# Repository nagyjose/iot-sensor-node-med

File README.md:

# IoT Sensor Node Medium (`iot-sensor-node-med`)

> Compact, battery-powered wireless IoT environmental monitoring node based on the Raspberry Pi Pico W, featuring Li-Ion charging, hardware battery protection, zero-quiescent voltage monitoring, and multiple sensor/display interfaces.

**Project Status:** Completed & Functional | **Technologies:** Autodesk Eagle, Hardware PCB Design, RP2040 / Pico W, MicroPython / C++

---

## 1. Overview & Key Features

The **IoT Sensor Node Medium** is a dedicated hardware board tailored for low-power remote environmental sensing, smart home telemetry, and weather monitoring. Designed around the **Raspberry Pi Pico W** (RP2040 + CYW43439 Wi-Fi & Bluetooth LE), the board integrates all necessary power management, battery safety circuitry, and sensor interfaces on a compact 49 × 74 mm two-layer PCB.

### Key Highlights
- **Microcontroller:** Raspberry Pi Pico W socket (RP2040 dual-core ARM Cortex-M0+ up to 133 MHz, 264 KB SRAM, 2 MB QSPI Flash, onboard 2.4 GHz 802.11n Wi-Fi and BLE 5.2).
- **Power Architecture:**
  - Standard 18650 Li-Ion / Li-Po single-cell battery holder footprint.
  - **Microchip MCP73831T** linear Li-Ion charge management IC with charging indicator LED (`D1`).
  - **Diodes Inc. AP9101C** dedicated battery protection controller paired with **BXT280N02B** dual N-MOSFET (overcharge, overdischarge cutoff, and short-circuit protection).
  - **Automatic Power Path:** Ultra-low drop P-channel MOSFET (`YJL2301D`) power switch and Schottky diode (`STPS1L30`) automatically transition between USB 5 V (VBUS) and battery power.
- **Ultra-Low Power Battery Monitoring:**
  - **LM4040** precision shunt voltage reference on the RP2040 `ADC_REF` pin for rock-solid ADC measurements regardless of supply variations.
  - Switched resistor divider (8.2 kΩ / 22 kΩ) controlled via GP3 (`EN-MEAS-1`) using dual MOSFETs (`T4` / `T6`). Zero current is consumed by the voltage divider during deep sleep!
  - Analog input clamped with dual Schottky diodes (`RB751V40T1G`) to protect the RP2040 ADC input (`GP27`).
- **Telemetry & Sensor Interfaces:**
  - **AM2302 (DHT22):** Relative humidity and ambient temperature digital sensor on `GP14`.
  - **DS18B20:** 1-Wire high-accuracy digital temperature sensor on `GP15`.
  - **OLED Display Header:** 4-pin header for 0.96" or 1.3" I2C OLED displays (SSD1306 / SH1106) on `I2C0` (`GP4` / `GP5`).
  - **nRF24L01+ 2.4 GHz RF Header:** SPI socket for Nordic nRF24L01+ wireless transceiver module on `SPI0` (`GP16`–`GP20`) for long-range ultra-low-power radio mesh networks.
  - **General Purpose Breakout:** Available headers for `UART0` (TX/RX), additional ADC channels (`GP26`, `GP28`), and multiple digital GPIOs.

---

## 2. Architecture & Block Diagram

```mermaid
flowchart TD
    subgraph PowerSystem["⚡ Power Management & Protection"]
        USB["USB 5V (VBUS)"] --> CHG["MCP73831T<br/>Li-Ion Charger"]
        USB --> PATH["Power Path Switch<br/>(P-MOS T3 & D3)"]
        BAT["18650 Li-Ion Cell"] --> PROT["AP9101C + Dual NMOS<br/>Battery Protection"]
        CHG --> PROT
        PROT --> PATH
        PATH --> VSYS["VSYS (System Rail)"]
        VSYS --> PICO_REG["Pico W Onboard RT6154<br/>Buck-Boost Converter"]
        PICO_REG --> 3V3["3.3V Power Rail"]
    end

    subgraph Monitoring["🔋 Precision Battery Measurement"]
        PROT -->|VBATT| DIV["Switched Divider<br/>(8.2k / 22k)"]
        MCU -->|GP3: EN-MEAS-1| GATE["MOSFET Switch<br/>(T4 / T6)"]
        GATE --> DIV
        DIV -->|VADC-1| MCU_ADC["ADC1 (GP27)<br/>Clamped & Filtered"]
        VREF["LM4040 Precision Ref"] -->|ADC_REF| MCU_ADC
    end

    subgraph MCU["🧠 Processing & Core Connectivity"]
        PICO["Raspberry Pi Pico W<br/>(RP2040 MCU)"]
        WIFI["Onboard CYW43439<br/>Wi-Fi 802.11n & BLE 5.2"]
    end

    subgraph Peripherals["📡 Sensors & Communication"]
        DHT["AM2302 / DHT22<br/>(Humidity & Temp)"] ---|GP14| MCU
        DS["DS18B20<br/>(1-Wire Temp)"] ---|GP15| MCU
        OLED["OLED Display<br/>(SSD1306 / SH1106)"] ---|I2C0: GP4/GP5| MCU
        NRF["nRF24L01+ Module<br/>(2.4 GHz RF)"] ---|SPI0: GP16-GP20| MCU
        UART["UART0 Header<br/>(Serial Debug / GPS)"] ---|GP0 / GP1| MCU
    end

    3V3 --> MCU
    3V3 --> Peripherals
```

---

## 3. Schematic & Circuit Diagram

📄 [Open original high-resolution schematic (PDF)](Sensor-node_med.pdf)

---

## 4. Hardware Specifications & Pin Mapping

### Microcontroller Pin Allocation

| Pico W Pin | Eagle Net Name | Hardware Function / Connected Device | Notes |
| :--- | :--- | :--- | :--- |
| **GP0** | `UART0-TX` | Serial UART TX | Breakout header / Debug |
| **GP1** | `UART0-RX` | Serial UART RX | Breakout header / Debug |
| **GP2** | `EN-MEAS-0` | Auxiliary measurement enable | Reserved / expansion |
| **GP3** | `EN-MEAS-1` | Battery measurement enable | Gates T4 & T6 MOSFETs |
| **GP4** | `I2C0-SDA` | I2C Data bus | Connected to OLED header (pin 4) |
| **GP5** | `I2C0-SCK` | I2C Clock bus | Connected to OLED header (pin 3) |
| **GP6–GP13** | `GPIO-2`..`GPIO-9`| General-purpose digital I/O | Header breakout pins |
| **GP14** | `AM2302-DATA` | AM2302 / DHT22 Data line | Pulled up to 3.3V with 4.7 kΩ (R15) |
| **GP15** | `1-WIRE-DQ` | DS18B20 1-Wire Data line | Pulled up to 3.3V with 4.7 kΩ (R16) |
| **GP16** | `SPI0-MISO` | nRF24L01+ MISO | SPI0 Data in |
| **GP17** | `SPI0-CSN` | nRF24L01+ Chip Select Not | SPI0 CSN |
| **GP18** | `SPI0-SCK` | nRF24L01+ Clock | SPI0 SCK |
| **GP19** | `SPI0-MOSI` | nRF24L01+ MOSI | SPI0 Data out |
| **GP20** | `RADIO-EN` | nRF24L01+ Chip Enable (CE) | Radio TX/RX enable |
| **GP26** | `VADC-0` | ADC Channel 0 | External analog input |
| **GP27** | `VADC-1` | ADC Channel 1 | Switched battery voltage divider input |
| **GP28** | `VADC-2` | ADC Channel 2 | External analog input |
| **ADC_REF** | `ADC-REF` | RP2040 ADC Reference voltage | Tied to LM4040 precision shunt reference |

### Power & Battery Circuit Components

| Component | Part / Package | Value / Function | Description |
| :--- | :--- | :--- | :--- |
| **U1** | MCP73831T-2ACI/OT (SOT-23-5) | Li-Ion Linear Charger | $I_{CHG} = 1000V / R_{PROG} = 1000 / 2\,\text{k}\Omega \approx 500\,\text{mA}$ |
| **U2** | AP9101CA6-ANTRG1 (SOT-26) | Battery Protection IC | Overvoltage, undervoltage cutoff, overcurrent |
| **T1** | BXT280N02B (TSSOP-8) | Dual N-MOSFET (20V, 6A) | Low-side power cutoff switch for AP9101 |
| **T3** | YJL2301D (SOT-23) | P-MOSFET (-20V, -2.8A) | Low-loss automatic power path switch |
| **D3** | STPS1L30 (SMA) | Schottky Diode (30V, 1A) | VBUS reverse protection / power supply |
| **D13** | LM4040AIM3-2.5 or 3.0 (SOT-23) | Shunt Reference | Precision reference voltage for ADC |
| **T4 / T6** | BXT280N02B / YJL2301D | NMOS + PMOS Switch | Gates $V_{BATT}$ divider to prevent sleep discharge |

---

## 5. PCB Design & Physical Dimensions

- **PCB Dimensions:** 48.95 mm × 73.90 mm (1.93" × 2.91")
- **Layer Count:** 2 layers (Top Copper, Bottom Copper)
- **Mounting:** Rounded corners, designed to fit inside standard plastic enclosure or snap-fit 3D-printed housing.
- **Top Side:** Houses the Raspberry Pi Pico W module, OLED display header, nRF24L01+ socket, sensors, and status LEDs.
- **Bottom Side:** Accommodates the single 18650 spring battery clip (`CON_18650`), protection IC, and power path semiconductors.

---

## 6. Repository Structure

```text
.
├── docs/
│   └── images/
│       └── schematic.png  # High-resolution schematic preview (180 DPI)
├── Sensor-node_med.sch    # Autodesk Eagle schematic
├── Sensor-node_med.brd    # Autodesk Eagle PCB layout
├── Sensor-node_med.pdf    # Complete schematic and board PDF documentation
├── Sensor-node_med.dru    # Design rules specification (DRC)
├── Sensor-node_med.scr    # Eagle layer & color setup script
├── .gitignore             # Eagle & OS backup filter
└── README.md              # Project documentation
```

---

## 7. How to Use & Firmware Deployment

### Hardware Assembly & Inspection
1. Inspect PCB solder joints around the SOT-23 and SOT-26 packages (`MCP73831T`, `AP9101C`, MOSFETs).
2. Insert a standard protected or unprotected 18650 cell into the battery clips observing correct polarity.
3. Plug in USB: `D1` will illuminate while charging and extinguish when charging completes.

### Firmware Support
This board is fully compatible with MicroPython, CircuitPython, and C/C++ (Pico SDK / Arduino IDE).
To read the battery voltage with zero idle power draw in MicroPython:

```python
from machine import Pin, ADC
import time

# Enable battery measurement divider
en_meas = Pin(3, Pin.OUT)
adc_bat = ADC(Pin(27))

def read_battery_voltage():
    en_meas.value(1)       # Power on the resistor divider
    time.sleep_us(50)      # Wait for rail stabilization
    raw = adc_bat.read_u16()
    en_meas.value(0)       # Immediately shut down divider to save battery

    # Conversion formula based on 8.2k / 22k divider ratio and reference voltage
    v_measured = (raw / 65535.0) * 3.3
    v_batt = v_measured * (8.2 + 22.0) / 22.0
    return v_batt
```

---

## 8. Relations & Ecosystem Links

This project is part of a modular IoT sensor ecosystem:
- **[`iot-sensor-node-max`](https://github.com/nagyjose/iot-sensor-node-max):** Sister project providing a dual-18650 battery bank, dual independent chargers, dual I2C expansion headers, dual SPI expansion headers, and external ADC input.
- **[`pico-w-iot-nodes`](https://github.com/nagyjose/pico-w-iot-nodes):** MicroPython firmware repository implementing BLE GATT telemetry, MQTT over Wi-Fi, DS18B20 / AM2302 acquisition, and deep sleep cycles.
- **[`ble-sensor-gui`](https://github.com/nagyjose/ble-sensor-gui):** PyQt5 / QML desktop application for real-time visualization of telemetry and sensor feeds.

---

## 9. License & Author

- **Author:** Josef Nagy (`nagyjose`)
- **Design Tool:** Autodesk Eagle v9.x
- **License:** Open Hardware / MIT License

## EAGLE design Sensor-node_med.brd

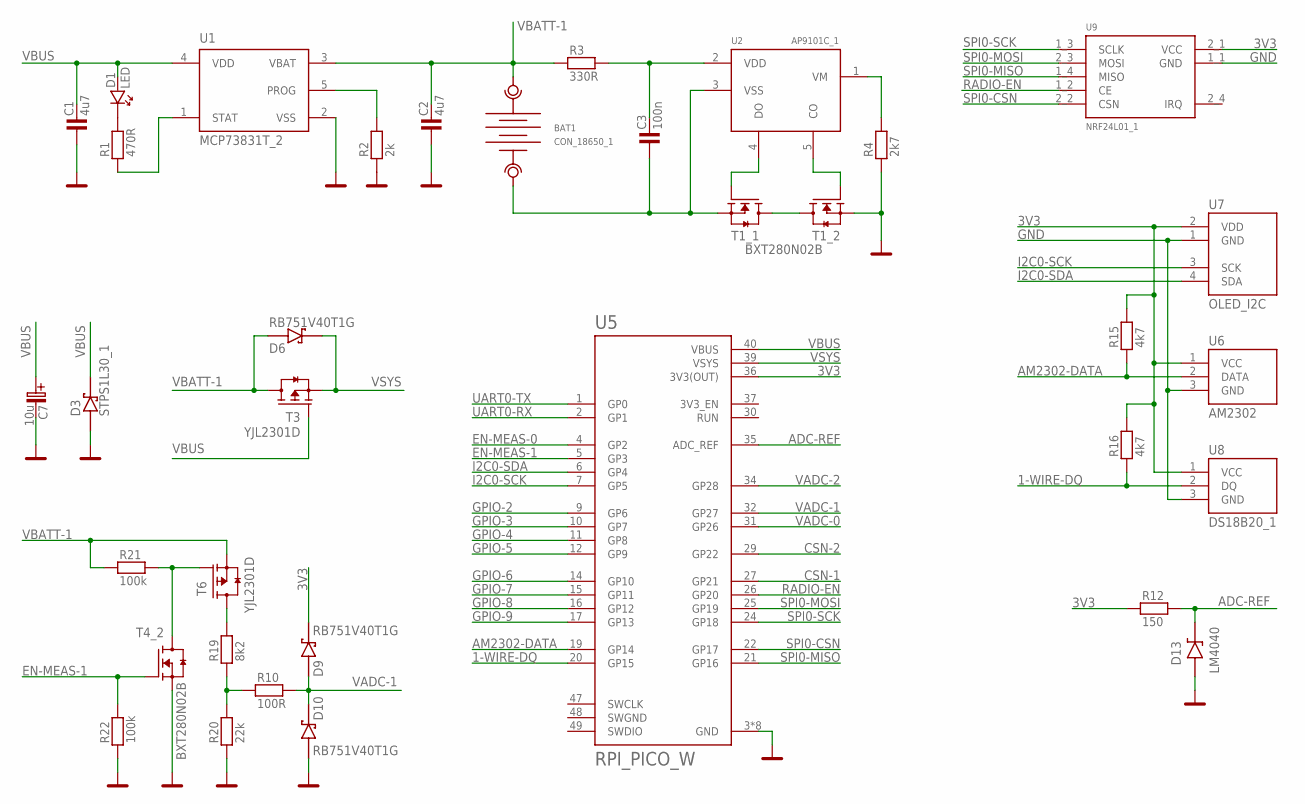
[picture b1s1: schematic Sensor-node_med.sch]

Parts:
BAT1: CON_18650_1; BATTERY_PADS_1
C1, C2: 4u7; 0805
C3: 100n; 0805
C7: 10u; C_EL-SMD_D
D1: LED; P1206
D3: STPS1L30_1; SMA
D6, D9, D10: RB751V40T1G; SOD323
D13: LM4040; TRANSISTOR-FET_SOT23
R1: 470R; 0805
R2: 2k; 0805
R3: 330R; 0805
R4: 2k7; 0805
R10: 100R; 0805
R12: 150; 0805
R15, R16: 4k7; 0805
R19: 8k2; 0805
R20: 22k; 0805
R21, R22: 100k; 0805
T1, T4: BXT280N02B; SO8
T3, T6: YJL2301D; TRANSISTOR-FET_SOT23
U1: MCP73831T_2; GHI-IC_SOT23-5(MICROCHIP)
U2: AP9101C_1; GHI-IC_SOT23-5(MICROCHIP)
U5: RPI_PICO_W
U6: AM2302
U7: OLED_I2C; I2C_CONN
U8: DS18B20_1; DS18B20_CABLE
U9: NRF24L01_1; NRF24L01_NORM

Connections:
1-WIRE-DQ: R16.1, U5.20 (GP15), U8.2 (DQ)
3V3: D9.1 (C), R12.1, R15.2, R16.2, U5.36 (3V3(OUT)), U6.1 (VCC), U7.2 (VDD), U8.1 (VCC), U9.2_1 (VCC)
ADC-REF: D13.1 (C), R12.2, U5.35 (ADC_REF)
AM2302-DATA: R15.1, U5.19 (GP14), U6.2 (DATA)
CO1: T1.2 (G), U2.5 (CO)
CSN-1: U5.27 (GP21)
CSN-2: U5.29 (GP22)
DO1: T1.4 (G), U2.4 (DO)
EN-MEAS-0: U5.4 (GP2)
EN-MEAS-1: R22.2, T4.2 (G), U5.5 (GP3)
GND: C1.1, C2.1, C7.- (C_EL-), D3.2 (A), D10.2 (A), D13.2 (A), R2.1, R4.1, R20.1, R22.1, T1.1 (S), T4.1 (S), U1.2 (VSS), U5.3 (GND), U5.8 (GND), U5.13 (GND), U5.18 (GND), U5.23 (GND), U5.28 (GND), U5.33 (GND), U5.38 (GND), U6.3 (GND), U7.1 (GND), U8.3 (GND), U9.1_1 (GND)
GPIO-2: U5.9 (GP6)
GPIO-3: U5.10 (GP7)
GPIO-4: U5.11 (GP8)
GPIO-5: U5.12 (GP9)
GPIO-6: U5.14 (GP10)
GPIO-7: U5.15 (GP11)
GPIO-8: U5.16 (GP12)
GPIO-9: U5.17 (GP13)
I2C0-SCK: U5.7 (GP5), U7.3 (SCK)
I2C0-SDA: U5.6 (GP4), U7.4 (SDA)
unnamed: D1.K, R1.2
unnamed: R21.2, T4.7 (D), T4.8 (D), T6.1 (G)
unnamed: R19.2, T6.3 (D)
unnamed: R10.1, R19.1, R20.2
NMOS-CONN-1: T1.5 (D), T1.6 (D), T1.7 (D), T1.8 (D)
P1-: BAT1.GND_1 (GND), BAT1.GND_2 (GND), C3.1, T1.3 (S), U2.3 (VSS)
PROG1: R2.2, U1.5 (PROG)
RADIO-EN: U5.26 (GP20), U9.1_2 (CE)
SPI0-CSN: U5.22 (GP17), U9.2_2 (CSN)
SPI0-MISO: U5.21 (GP16), U9.1_4 (MISO)
SPI0-MOSI: U5.25 (GP19), U9.2_3 (MOSI)
SPI0-SCK: U5.24 (GP18), U9.1_3 (SCLK)
STAT1: R1.1, U1.1 (STAT)
SWGND: U5.48 (SWGND)
UART0-RX: U5.2 (GP1)
UART0-TX: U5.1 (GP0)
VADC-0: U5.31 (GP26)
VADC-1: D9.2 (A), D10.1 (C), R10.2, U5.32 (GP27)
VADC-2: U5.34 (GP28)
VBATT-1: BAT1.UCC_1 (UCC), BAT1.UCC_2 (UCC), C2.2, D6.2 (A), R3.1, R21.1, T3.3 (D), T6.2 (S), U1.3 (VBAT)
VBUS: C1.2, C7.+ (C_EL+), D1.A, D3.1 (C), T3.1 (G), U1.4 (VDD), U5.40 (VBUS)
VDD-AP9101-1: C3.2, R3.2, U2.2 (VDD)
VM1: R4.2, U2.1 (VM)
VSYS: D6.1 (C), T3.2 (S), U5.39 (VSYS)

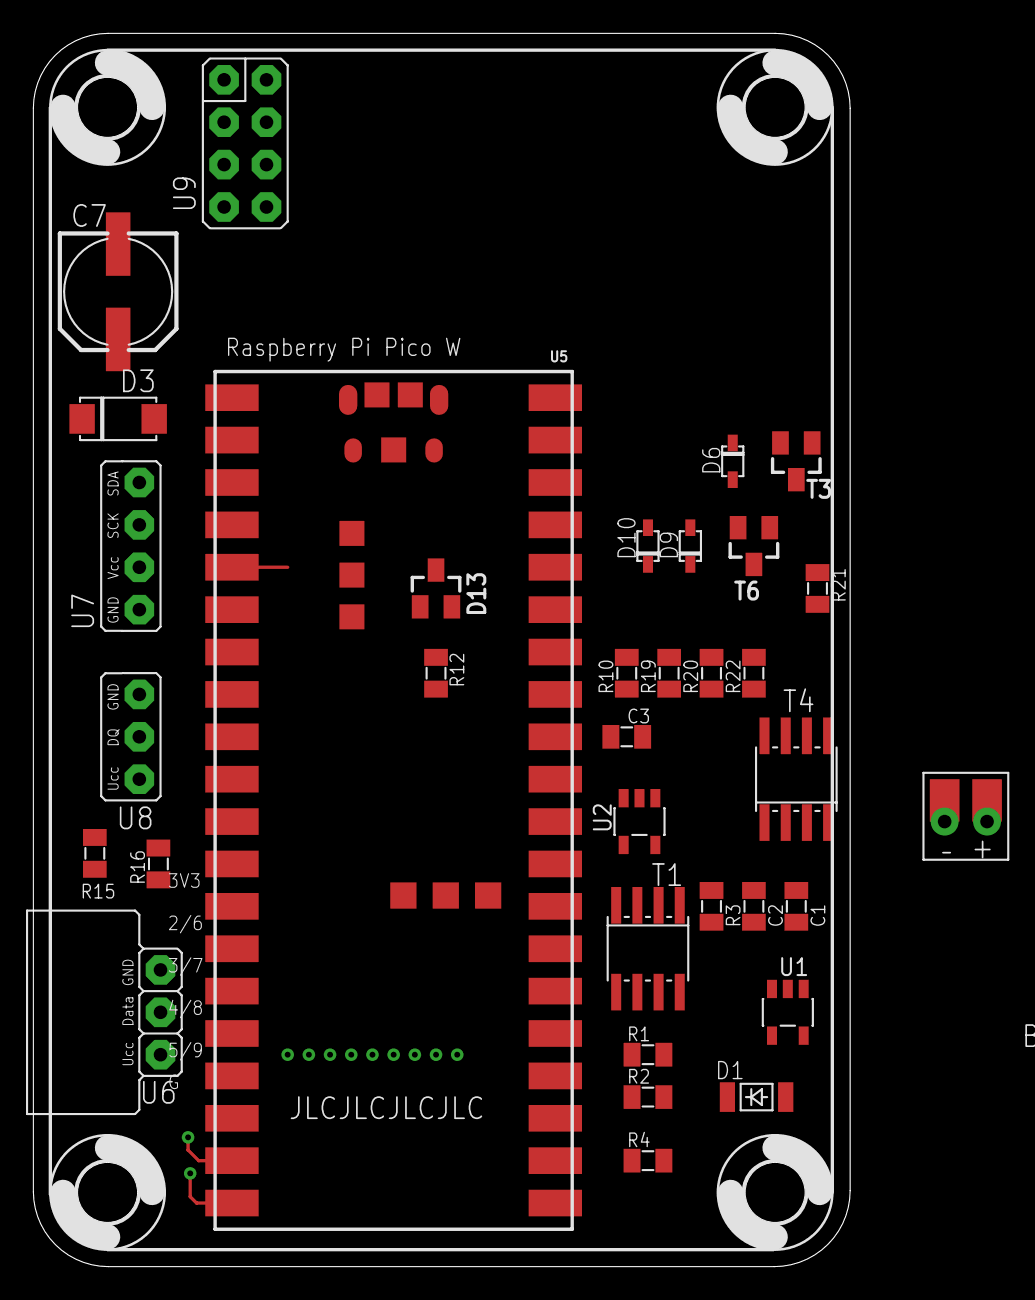
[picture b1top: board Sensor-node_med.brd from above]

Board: 2 copper layers, 48.9 x 73.9 mm, 38 parts (0 on the bottom side), 29 nets.

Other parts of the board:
U$1, U$2, U$3, U$4: 3,6

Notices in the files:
parts and their libraries:
Copyright (C) PaJa 2001-2014
